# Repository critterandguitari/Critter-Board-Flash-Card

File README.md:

Critter-Board-Flash-Card
========================

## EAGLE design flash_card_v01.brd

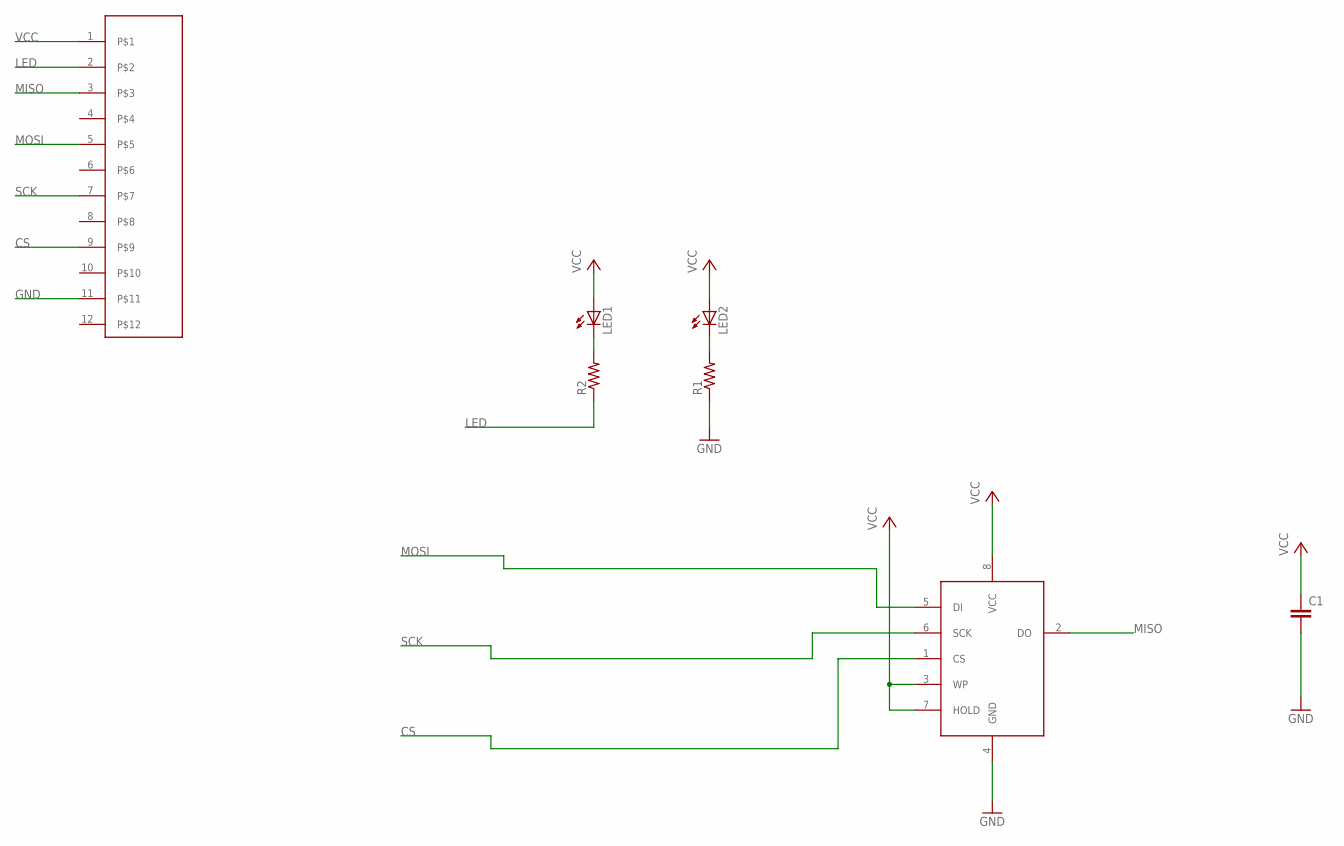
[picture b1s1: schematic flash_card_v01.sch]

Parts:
C1: CAP0603; C0603
LED1, LED2: LED1206; CHIPLED_1206
R1, R2: RES0603; R0603
U$1: M25PXX; SO08
U$2: SAMCARD6

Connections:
CS: U$1.1 (CS), U$2.9
GND: C1.2, R1.1, U$1.4 (GND), U$2.11
LED: R2.1, U$2.2
MISO: U$1.2 (DO), U$2.3
MOSI: U$1.5 (DI), U$2.5
unnamed: LED1.C, R2.2
unnamed: LED2.C, R1.2
SCK: U$1.6 (SCK), U$2.7
VCC: C1.1, LED1.A, LED2.A, U$1.3 (WP), U$1.7 (HOLD), U$1.8 (VCC), U$2.1

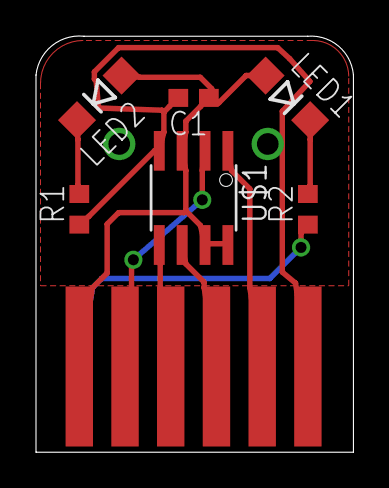
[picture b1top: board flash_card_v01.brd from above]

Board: 2 copper layers, 17.6 x 23.1 mm, 7 parts (0 on the bottom side), 9 nets.

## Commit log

2013-04-21 adding eagle files
